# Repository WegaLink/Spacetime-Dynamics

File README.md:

# Spacetime-Dynamics
Investigation of signals that potentially propagate through an elastic spacetime.

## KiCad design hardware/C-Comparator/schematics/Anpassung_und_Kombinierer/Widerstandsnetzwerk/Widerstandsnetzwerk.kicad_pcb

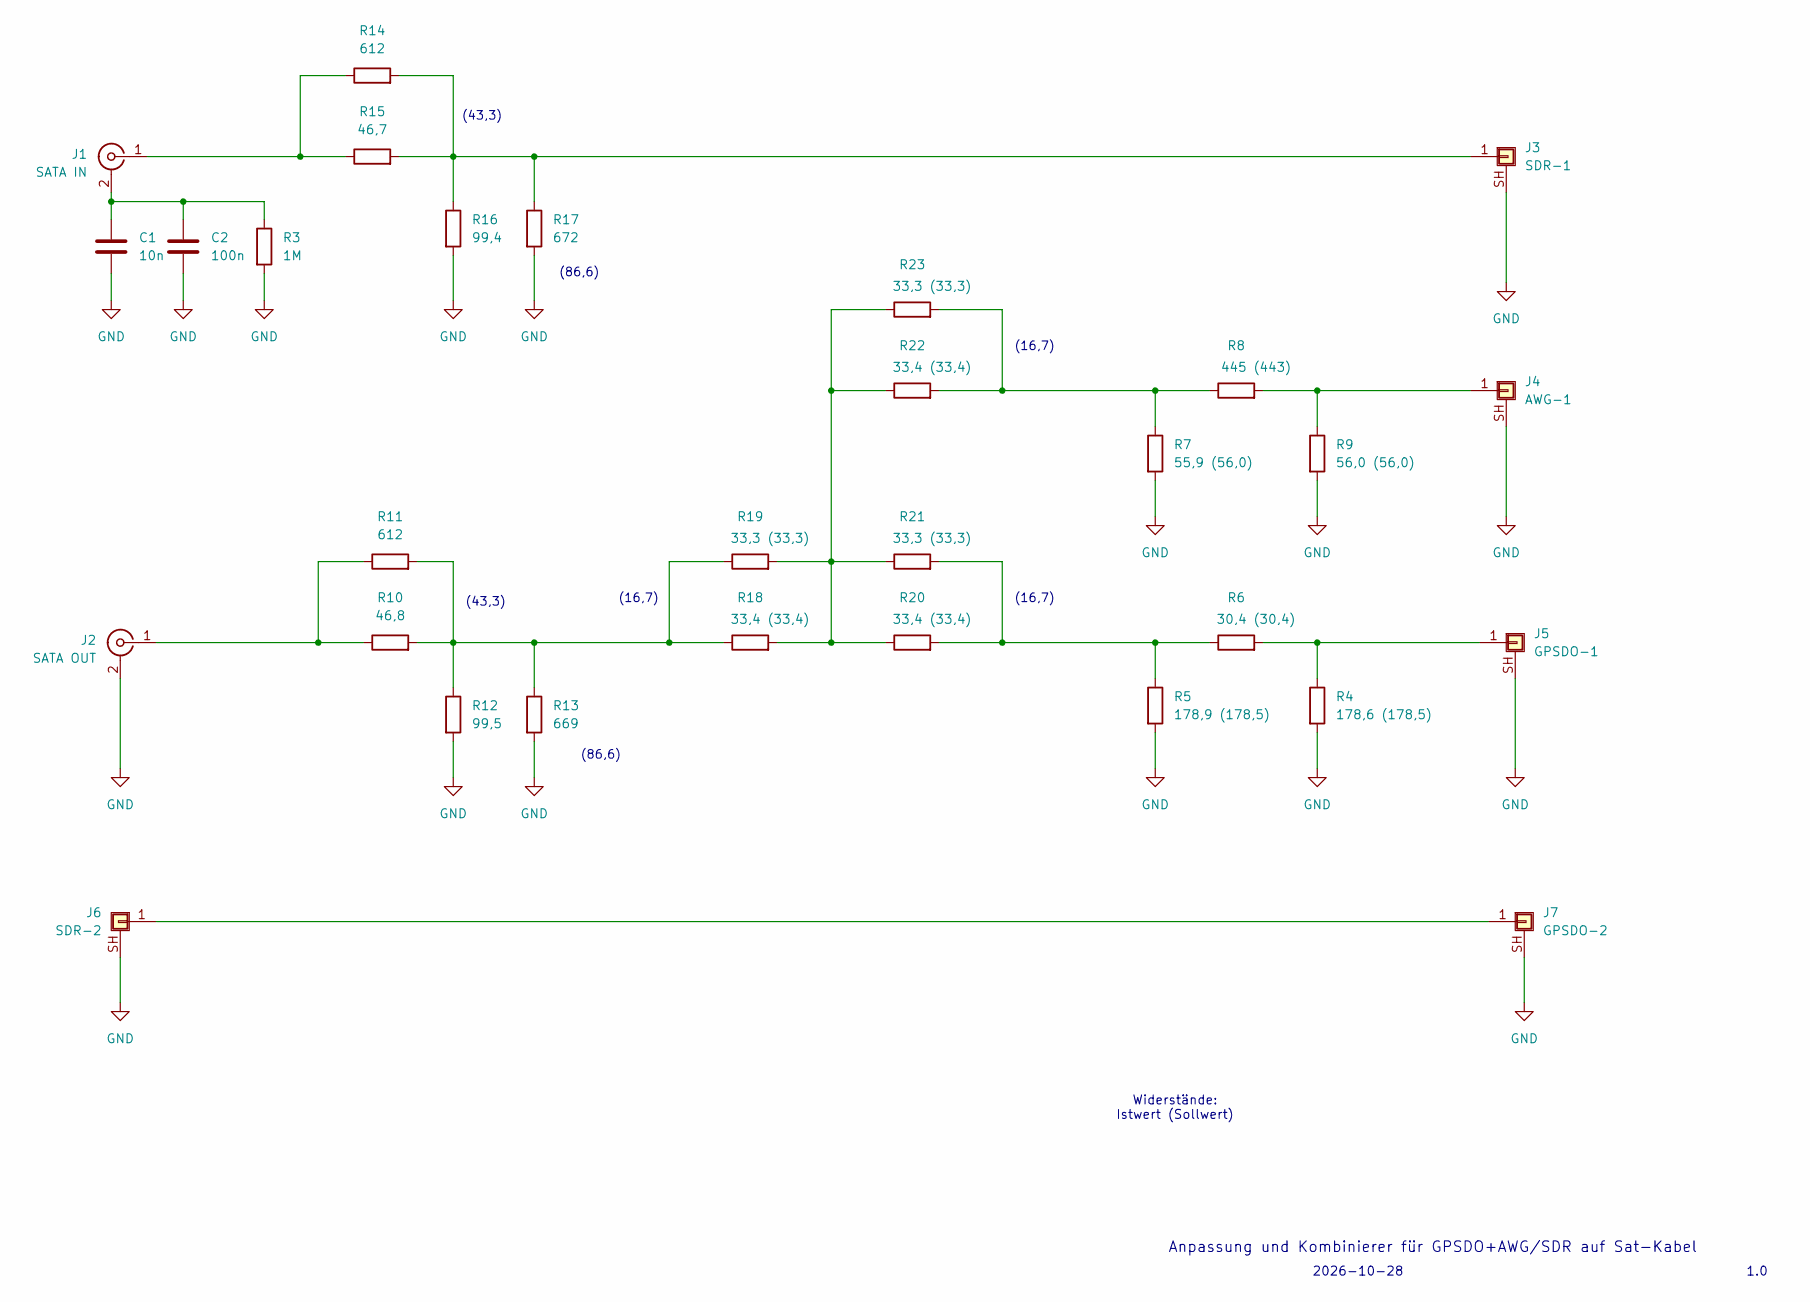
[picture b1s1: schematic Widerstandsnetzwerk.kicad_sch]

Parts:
C1: 10n; C_Disc_D4.3mm_W1.9mm_P5.00mm
C2: 100n; C_Disc_D4.3mm_W1.9mm_P5.00mm
J1: SATA IN; CONN_73330-0030_MOL
J2: SATA OUT; CONN_73330-0030_MOL
J3: SDR-1; SMA_Amphenol_132291_Vertical
J4: AWG-1; SMA_Amphenol_132291_Vertical
J5: GPSDO-1; SMA_Amphenol_132291_Vertical
J6: SDR-2; SMA_Amphenol_132291_Vertical
J7: GPSDO-2; SMA_Amphenol_132291_Vertical
R3: 1M; R_Axial_DIN0309_L9.0mm_D3.2mm_P12.70mm_Horizontal
R4: 178,6 (178,5); R_Axial_DIN0309_L9.0mm_D3.2mm_P12.70mm_Horizontal
R5: 178,9 (178,5); R_Axial_DIN0309_L9.0mm_D3.2mm_P12.70mm_Horizontal
R6: 30,4 (30,4); R_Axial_DIN0309_L9.0mm_D3.2mm_P12.70mm_Horizontal
R7: 55,9 (56,0); R_Axial_DIN0309_L9.0mm_D3.2mm_P12.70mm_Horizontal
R8: 445 (443); R_Axial_DIN0309_L9.0mm_D3.2mm_P12.70mm_Horizontal
R9: 56,0 (56,0); R_Axial_DIN0309_L9.0mm_D3.2mm_P12.70mm_Horizontal
R10: 46,8; R_Axial_DIN0309_L9.0mm_D3.2mm_P12.70mm_Horizontal
R11, R14: 612; R_Axial_DIN0309_L9.0mm_D3.2mm_P12.70mm_Horizontal
R12: 99,5; R_Axial_DIN0309_L9.0mm_D3.2mm_P12.70mm_Horizontal
R13: 669; R_Axial_DIN0309_L9.0mm_D3.2mm_P12.70mm_Horizontal
R15: 46,7; R_Axial_DIN0309_L9.0mm_D3.2mm_P12.70mm_Horizontal
R16: 99,4; R_Axial_DIN0309_L9.0mm_D3.2mm_P12.70mm_Horizontal
R17: 672; R_Axial_DIN0309_L9.0mm_D3.2mm_P12.70mm_Horizontal
R18, R20, R22: 33,4 (33,4); R_Axial_DIN0309_L9.0mm_D3.2mm_P12.70mm_Horizontal
R19, R21, R23: 33,3 (33,3); R_Axial_DIN0309_L9.0mm_D3.2mm_P12.70mm_Horizontal

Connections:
GND: C1.2, C2.2, J2.2 (Ext), J3.SH (Shield), J4.SH (Shield), J5.SH (Shield), J6.SH (Shield), J7.SH (Shield), R3.2, R4.2, R5.2, R7.2, R9.2, R12.2, R13.2, R16.2, R17.2
unnamed: C1.1, C2.1, J1.2 (Ext), R3.1
unnamed: J1.1 (In), R14.1, R15.1
unnamed: J2.1 (In), R10.1, R11.1
unnamed: J3.1, R14.2, R15.2, R16.1, R17.1
unnamed: J4.1, R8.2, R9.1
unnamed: J5.1, R4.1, R6.2
unnamed: J6.1, J7.1
unnamed: R10.2, R11.2, R12.1, R13.1, R18.1, R19.1
unnamed: R18.2, R19.2, R20.1, R21.1, R22.1, R23.1
unnamed: R5.1, R6.1, R20.2, R21.2
unnamed: R7.1, R8.1, R22.2, R23.2

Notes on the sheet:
1.0
(43,3)
(16,7)
(86,6)
Anpassung und Kombinierer für GPSDO+AWG/SDR auf Sat-Kabel
Widerstände: Istwert (Sollwert)
2026-10-28

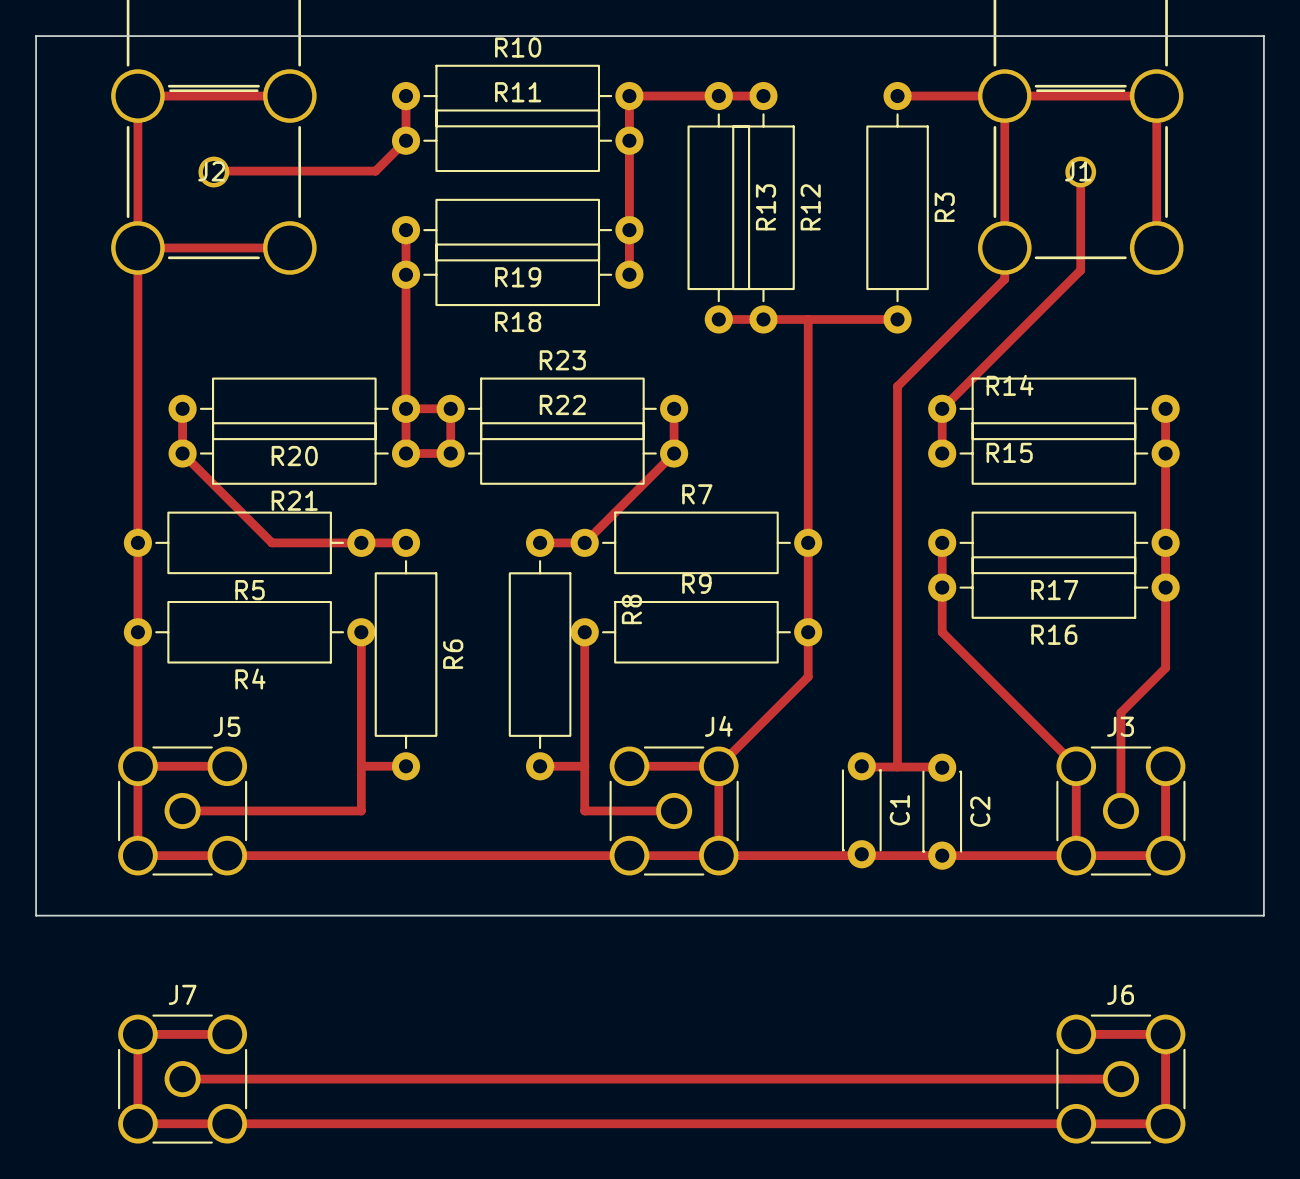
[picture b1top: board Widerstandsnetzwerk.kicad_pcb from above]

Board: 2 copper layers, 69.8 x 50.0 mm, 30 parts (0 on the bottom side), 12 nets.

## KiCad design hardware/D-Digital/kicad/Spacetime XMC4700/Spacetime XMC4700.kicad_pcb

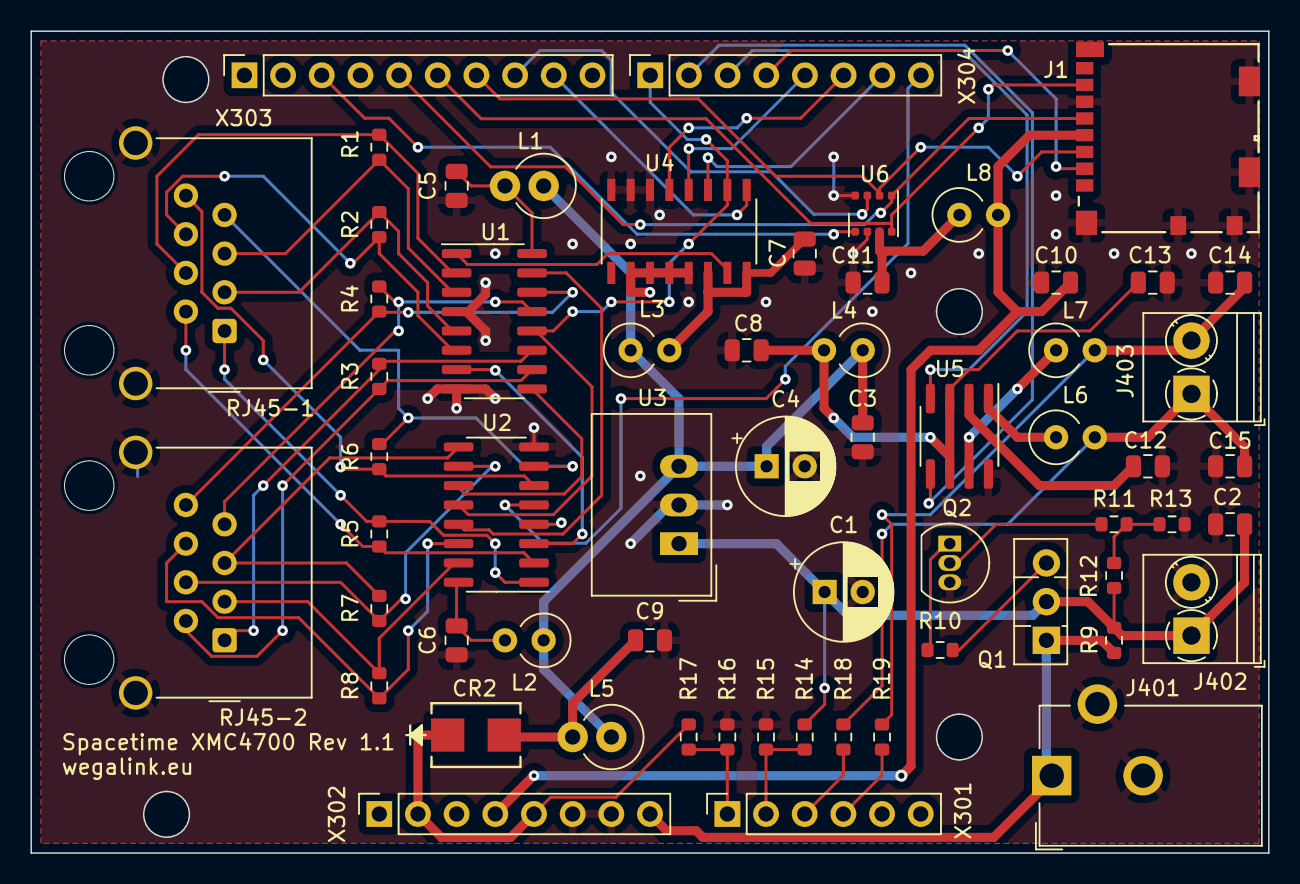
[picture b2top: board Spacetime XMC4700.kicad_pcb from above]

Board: 2 copper layers, 81.3 x 54.0 mm, 61 parts (0 on the bottom side), 59 nets.

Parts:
C1, C4: 100µ 16V; CP_Radial_D6.3mm_P2.50mm
C2, C3, C5, C6, C7, C8, C9, C10, C11: 100n; C_0805_2012Metric
C12, C13, C14, C15: 4.7µ; C_0805_2012Metric
CR2: SS24; DIODE_DO214AA
J1: Micro_SD_Card; 104031-0811_MOL
J401: Jack-DC; BarrelJack_CUI_PJ-102AH_Horizontal
J402: Screw_Terminal_01x02; TerminalBlock_Phoenix_PT-1,5-2-3.5-H_1x02_P3.50mm_Horizontal
J403: Screw_terminal_01x02; TerminalBlock_Phoenix_PT-1,5-2-3.5-H_1x02_P3.50mm_Horizontal
L1: 100µ / 200mA; L_Axial_L9.5mm_D4.0mm_P2.54mm_Vertical_Fastron_SMCC
L2, L8: 100µ / 20mA; L_Axial_L7.0mm_D3.3mm_P2.54mm_Vertical_Fastron_MICC
L3, L4: 100µ / 50mA; L_Axial_L7.0mm_D3.3mm_P2.54mm_Vertical_Fastron_MICC
L5: 100µ / 350mA; L_Axial_L9.5mm_D4.0mm_P2.54mm_Vertical_Fastron_SMCC
L6, L7: 100µ / 100mA; L_Axial_L7.0mm_D3.3mm_P2.54mm_Vertical_Fastron_MICC
Q1: BD136; TO-126-3_Vertical
Q2: BC546A; TO-92_Inline
R1, R2, R3, R4, R5, R6, R7, R8: 100; R_0603_1608Metric
R9: 6k8; R_0603_1608Metric
R10, R13: 2k7; R_0603_1608Metric
R11: 47k; R_0603_1608Metric
R12: 5k6; R_0603_1608Metric
R14: 10k; R_0603_1608Metric
R15, R16, R17: 2k2; R_0603_1608Metric
R18, R19: 1k; R_0603_1608Metric
RJ45-1: RJ45-IN/OUT; RJ45_Wuerth_7499010001A_Horizontal
RJ45-2: RJ45-reflector; RJ45_Wuerth_7499010001A_Horizontal
U1: LTC1688; SOIC-16_3.9x9.9mm_P1.27mm
U2: LTC1518; SOIC-16_3.9x9.9mm_P1.27mm
U3: TSR_2-2450; Converter_DCDC_TRACO_TSR-1_THT
U4: DS1023-25; ds1023-25
U5: ZXBM5210; SOIC-8_3.9x4.9mm_P1.27mm
U6: BME680; Bosch_LGA-8_3x3mm_P0.8mm_ClockwisePinNumbering
X301: PRT-09280 Arduino stackable header 6 pin; PinSocket_1x06_P2.54mm_Vertical
X302, X304: PRT-09279 Arduino stackable header 8 pin; PinSocket_1x08_P2.54mm_Vertical
X303: PRT-11376 Arduino stackable header 10 pin; PinSocket_1x10_P2.54mm_Vertical

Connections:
/BAT+12: C1.1, C2.2, J402.1 (+12V), Q1.2 (C), R9.1, R12.1, R14.2, U3.1 (Vin)
/BME_CS: U6.2 (CSB), X303.8 (P3.10)
/PELTDN: C14.2, J403.2, L7.2, R19.2
/PELTUP: C15.2, J403.1, L6.2, R18.2
/SD_CS: J1.2 (DAT3/CD), X304.4 (P1.8)
/SERCLK: U4.4 (CLK/P1), X304.5 (P1.1)
/SERDAT: U4.5 (D/P2), X304.6 (P1.0)
/SERENA: U1.12 (~EN), U2.12 (~EN), U4.2 (LE), X304.1 (P1.9)
/SIDELA: U1.1 (DI1), U4.15 (OUT/*OUT)
/SIGOUT: U4.1 (IN), X303.9 (P1.11)
/SPI_CLK: J1.5 (CLK), U6.4 (SCK), X303.5 (P3.9)
/SPI_MISO: J1.7 (DAT0), U6.5 (SDO), X303.6 (P3.7)
/SPI_MOSI: J1.3 (CMD), U6.3 (SDI), X303.7 (P3.8)
/TEMPDN: U5.5 (REV), X304.2 (P2.11)
/TEMPUP: U5.4 (FWD), X304.3 (P2.12)
/VAREF: U6.8 (VDD), X303.3 (VAREF)
/VCC3: C7.2, L3.2, U4.14 (*P/S), U4.16 (VCC)
/VDD1: C5.2, L1.2, U1.16 (VDD)
/VDD2: C6.2, L2.2, U2.16 (VDD)
/VDD4: C8.2, C13.2, L4.2, U5.3 (VDD), U5.6 (VREF)
/VDD5: C9.2, CR2.2, L5.2
/VIN+12: J401.1, Q1.1 (E), R9.2, X302.8 (N.C.)
GND: C1.2, C2.1, C3.1, C4.2, C5.1, C6.1, C7.1, C8.1, C9.1, C10.1, C11.1, C12.1, C13.1, C14.1, C15.1, J1.6 (VSS), J1.9 (SHIELD), J1.10, J1.11, J1.13, J1.14, J401.2, J401.3, J402.2 (GND), Q2.3 (E), R13.2, R15.1, R16.1, RJ45-1.SH, RJ45-2.SH, U1.4 (EN), U1.8 (GND), U2.4 (EN), U2.8 (GND), U3.2 (GND), U4.6 (P3), U4.7 (P4), U4.8 (GND), U4.10 (P5), U4.11 (MS), U4.12 (P6), U4.13 (P7), U5.8 (GND), U6.1 (GND), U6.7 (GND), X302.6 (GND), X302.7 (GND)
unnamed: C10.2, J1.4 (VDD), L8.2, X302.4 (3V3)
unnamed: Q1.3 (B), R10.2
unnamed: Q2.2 (B), R11.2
unnamed: Q2.1 (C), R10.1
unnamed: R11.1, R12.2, R13.1
unnamed: R1.1, RJ45-1.4 (bl), U1.2 (DO1A)
unnamed: R6.1, RJ45-1.8 (br), U2.6 (A2)
unnamed: R2.1, RJ45-1.6 (gn), U1.6 (DO2A)
unnamed: R5.1, RJ45-1.2 (or), U2.2 (A1)
unnamed: R1.2, RJ45-1.5 (w/bl), U1.3 (DO1B)
unnamed: R6.2, RJ45-1.7 (w/br), U2.7 (B2)
unnamed: R2.2, RJ45-1.3 (w/gn), U1.5 (DO2B)
unnamed: R5.2, RJ45-1.1 (w/or), U2.1 (B1)
unnamed: R7.1, RJ45-2.4 (bl), U2.10 (A3)
unnamed: R4.1, RJ45-2.8 (br), U1.14 (DO4A)
unnamed: R8.1, RJ45-2.6 (gn), U2.14 (A4)
unnamed: R3.1, RJ45-2.2 (or), U1.10 (DO3A)
unnamed: R7.2, RJ45-2.5 (w/bl), U2.9 (B3)
unnamed: R4.2, RJ45-2.7 (w/br), U1.13 (DO4B)
unnamed: R8.2, RJ45-2.3 (w/gn), U2.15 (B4)
unnamed: R3.2, RJ45-2.1 (w/or), U1.11 (DO3B)
unnamed: U1.7 (DI2), U2.3 (Out1)
unnamed: U1.9 (DI3), U2.11 (Out3)
unnamed: U1.15 (DI4), U2.13 (Out4)
unnamed: U2.5 (Out2), X304.8 (P2.15)
unnamed: C3.2, C4.1, L1.1, L2.1, L3.1, L4.1, L5.1, U3.3 (Vout)
unnamed: U4.3 (Q/P0), X304.7 (P2.14)
unnamed: L6.1, U5.1 (OUT1)
unnamed: L7.1, U5.7 (OUT2)
unnamed: C12.2, U5.2 (VM)
unnamed: C11.2, L8.1, U6.6 (VDDIO)
unnamed: R16.2, R17.2, X301.1 (P14.0)
unnamed: R14.1, R15.2, X301.2 (P14.1)
unnamed: R18.1, X301.3 (P14.2)
unnamed: R19.1, X301.4 (P14.3)
unnamed: CR2.1, R17.1, X302.2 (IOREF), X302.5 (5V)

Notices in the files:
parts and their libraries:
Copyright 2021 Accelerated Designs. All rights reserved.
